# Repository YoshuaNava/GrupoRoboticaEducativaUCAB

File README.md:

Grupo de Robotica Educativa UCAB
================================

Repositorio de materiales, programas, documentos, diagramas de circuito, fotos y demás, de los proyectos de servicio comunitario y voluntariado.

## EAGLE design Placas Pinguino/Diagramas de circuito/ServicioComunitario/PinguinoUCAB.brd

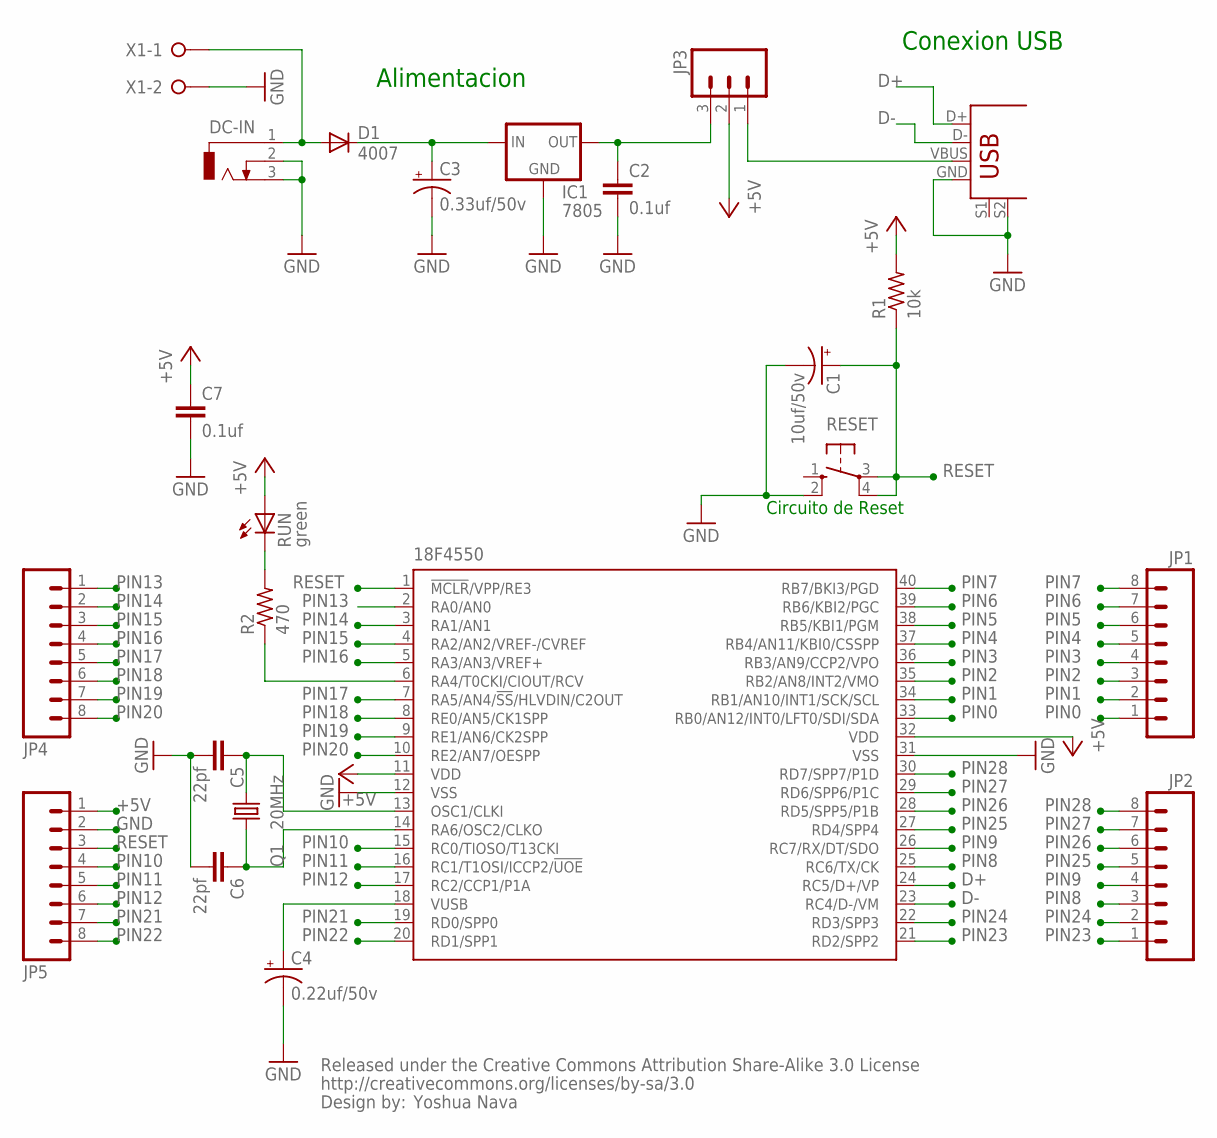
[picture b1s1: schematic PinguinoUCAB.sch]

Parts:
18F4550: PIC18F4550_40; DIL40
C1: 10uf/50v; CPOL-RADIAL-10UF-25V
C2, C7: 0.1uf; CAP-PTH-SMALL2
C3: 0.33uf/50v; CPOL-RADIAL-10UF-25V
C4: 0.22uf/50v; CPOL-RADIAL-10UF-25V
C5, C6: 22pf; CAP-PTH-SMALL2
CC_TEXT1: CREATIVE_COMMONS
D1: 4007; DO35-7
DC-IN: DCJ0303
IC1: 7805; 78XXL
JP1, JP2, JP4, JP5: 1X08_LONGPADS
JP3: 1X03_LONGPADS
Q1: 20MHz; HC49U-V
R1: 10k; 0207/7
R2: 470; 0207/7
RESET: B3F-10XX
RUN: green; LED3MM
USB: USB+SHIELD; USB-B-PTH
X1: W237-132

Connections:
+5V: 18F4550.11 (VDD), 18F4550.32 (VDD), C7.1, JP3.2, JP5.1, R1.2, RUN.A
D+: 18F4550.24 (RC5/D+/VP), USB.D+
D-: 18F4550.23 (RC4/D-/VM), USB.D-
GND: 18F4550.12 (VSS), 18F4550.31 (VSS), C1.2 (-), C2.2, C3.2 (-), C4.2 (-), C5.2, C6.2, C7.2, DC-IN.2, DC-IN.3, IC1.GND, JP5.2, RESET.2 (S1), USB.GND, USB.S2, X1.2
unnamed: 18F4550.13 (OSC1/CLKI), C5.1, Q1.1
unnamed: C3.1 (+), D1.C, IC1.IN
unnamed: C2.1, IC1.OUT, JP3.3
unnamed: JP3.1, USB.VBUS
unnamed: 18F4550.14 (RA6/OSC2/CLKO), C6.1, Q1.2
unnamed: 18F4550.18 (VUSB), C4.1 (+)
unnamed: R2.2, RUN.K (C)
unnamed: 18F4550.6 (RA4/T0CKI/CIOUT/RCV), R2.1
unnamed: D1.A, DC-IN.1, X1.1
PIN0: 18F4550.33 (RB0/AN12/INT0/LFT0/SDI/SDA), JP1.1
PIN1: 18F4550.34 (RB1/AN10/INT1/SCK/SCL), JP1.2
PIN2: 18F4550.35 (RB2/AN8/INT2/VMO), JP1.3
PIN3: 18F4550.36 (RB3/AN9/CCP2/VPO), JP1.4
PIN4: 18F4550.37 (RB4/AN11/KBI0/CSSPP), JP1.5
PIN5: 18F4550.38 (RB5/KBI1/PGM), JP1.6
PIN6: 18F4550.39 (RB6/KBI2/PGC), JP1.7
PIN7: 18F4550.40 (RB7/BKI3/PGD), JP1.8
PIN8: 18F4550.25 (RC6/TX/CK), JP2.3
PIN9: 18F4550.26 (RC7/RX/DT/SDO), JP2.4
PIN10: 18F4550.15 (RC0/TIOSO/T13CKI), JP5.4
PIN11: 18F4550.16 (RC1/T1OSI/ICCP2/!UOE), JP5.5
PIN12: 18F4550.17 (RC2/CCP1/P1A), JP5.6
PIN13: 18F4550.2 (RA0/AN0), JP4.1
PIN14: 18F4550.3 (RA1/AN1), JP4.2
PIN15: 18F4550.4 (RA2/AN2/VREF-/CVREF), JP4.3
PIN16: 18F4550.5 (RA3/AN3/VREF+), JP4.4
PIN17: 18F4550.7 (RA5/AN4/!SS!/HLVDIN/C2OUT), JP4.5
PIN18: 18F4550.8 (RE0/AN5/CK1SPP), JP4.6
PIN19: 18F4550.9 (RE1/AN6/CK2SPP), JP4.7
PIN20: 18F4550.10 (RE2/AN7/OESPP), JP4.8
PIN21: 18F4550.19 (RD0/SPP0), JP5.7
PIN22: 18F4550.20 (RD1/SPP1), JP5.8
PIN23: 18F4550.21 (RD2/SPP2), JP2.1
PIN24: 18F4550.22 (RD3/SPP3), JP2.2
PIN25: 18F4550.27 (RD4/SPP4), JP2.5
PIN26: 18F4550.28 (RD5/SPP5/P1B), JP2.6
PIN27: 18F4550.29 (RD6/SPP6/P1C), JP2.7
PIN28: 18F4550.30 (RD7/SPP7/P1D), JP2.8
RESET: 18F4550.1 (!MCLR!/VPP/RE3), C1.1 (+), JP5.3, R1.1, RESET.3, RESET.4 (P1)

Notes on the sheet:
Alimentacion
Conexion USB
Circuito de Reset
Yoshua Nava

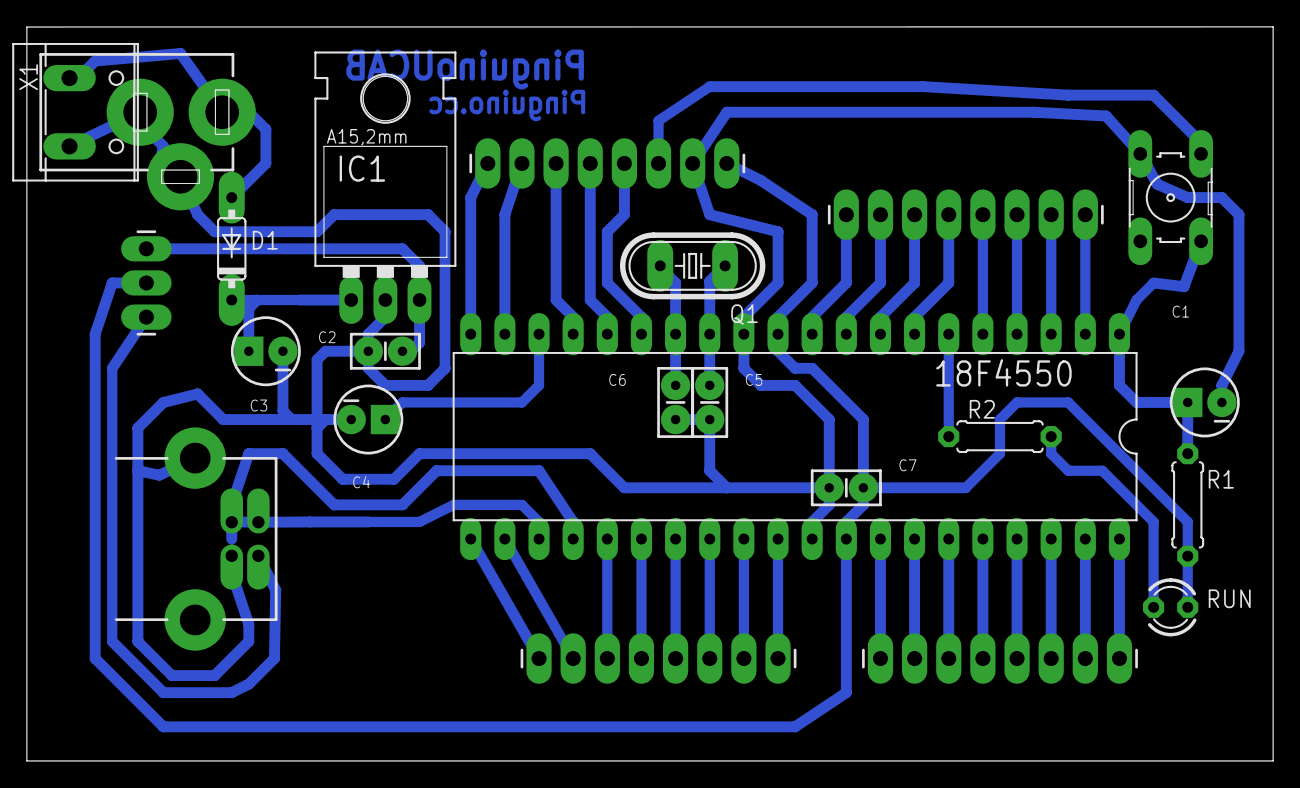
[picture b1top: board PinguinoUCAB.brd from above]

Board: 2 copper layers, 92.7 x 54.6 mm, 24 parts (0 on the bottom side), 43 nets.

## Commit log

2014-05-02 Primer Commit
2014-05-02 Tercer commit
2014-05-02 Cuarto commit
2014-05-02 Quinto commit
2014-05-02 Sexto commit
    Código para leer un caracter por USB e imprimirlo por pantalla.
2014-05-02 Septimo commit
    Nuevos tutoriales de .printf y comunicación serial en los manuales.
2014-05-16 Octavo commit
    Plantillas de LaTeX y comienzo de manual
2014-05-24 Manuales + Reorganización de carpetas
2014-06-04 Información diversa
    Tutorial de soldadura
2014-06-10 Diagramas de Circuito
    PinguinoUCAB-4550
2014-06-10 Diagramas de circuito
    Organizados archivos de PinguinoUCAB, y eliminada carpeta de
    PinguinoBase4550 (Se dejó el ZIP original que fue descargado de su
    repositorio).
2014-08-19 Diagramas de circuito.
2014-10-17 Bootloader
2014-10-17 Reorganización
2014-10-17 Drivers
2015-02-07 Manual de construcción.
2015-12-03 Hoja de materiales de la PinguinoUCAB4550, con precios actualizados (3 de diciembre de 2015).

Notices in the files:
parts and their libraries:
SparkFun-Aesthetics: Licensing: CC v3.0 Share-Alike You are welcome to use this library for commercial purposes.
SparkFun-Aesthetics: Released under the Creative Commons Attribution Share-Alike 3.0 License
SparkFun-Aesthetics: http://creativecommons.org/licenses/by-sa/3.0
